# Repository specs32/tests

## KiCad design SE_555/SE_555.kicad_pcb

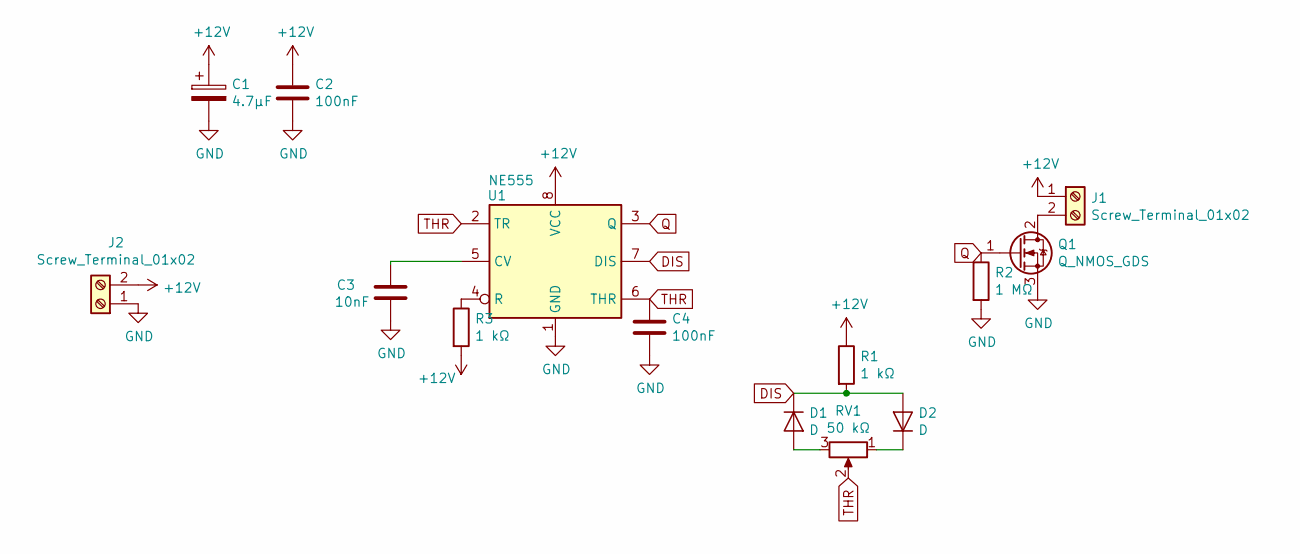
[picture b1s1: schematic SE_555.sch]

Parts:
C1: 4.7µF; CP_Radial_D6.3mm_P2.50mm
C2, C4: 100nF; C_Disc_D4.7mm_W2.5mm_P5.00mm
C3: 10nF; C_Disc_D4.7mm_W2.5mm_P5.00mm
D1, D2: D; D_A-405_P7.62mm_Horizontal
J1, J2: Screw_Terminal_01x02; TerminalBlock_bornier-2_P5.08mm
Q1: Q_NMOS_GDS; TO-220-3_Vertical
R1, R3: 1 kΩ; R_Axial_DIN0207_L6.3mm_D2.5mm_P7.62mm_Horizontal
R2: 1 MΩ; R_Axial_DIN0207_L6.3mm_D2.5mm_P7.62mm_Horizontal
RV1: 50 kΩ; Potentiometer_Bourns_3386C_Horizontal
U1: NE555; DIP-8_W7.62mm_LongPads

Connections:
+12V: C1.1, C2.1, J1.1, J2.2, R1.1, R3.2, U1.8 (VCC)
DIS: D1.1 (K), D2.2 (A), R1.2, U1.7 (DIS)
GND: C1.2, C2.2, C3.1, C4.2, J2.1, Q1.3 (S), R2.2, U1.1 (GND)
unnamed: C3.2, U1.5 (CV)
unnamed: D1.2 (A), RV1.3
unnamed: D2.1 (K), RV1.1
unnamed: J1.2, Q1.2 (D)
unnamed: R3.1, U1.4 (R)
Q: Q1.1 (G), R2.1, U1.3 (Q)
THR: C4.1, RV1.2, U1.2 (TR), U1.6 (THR)

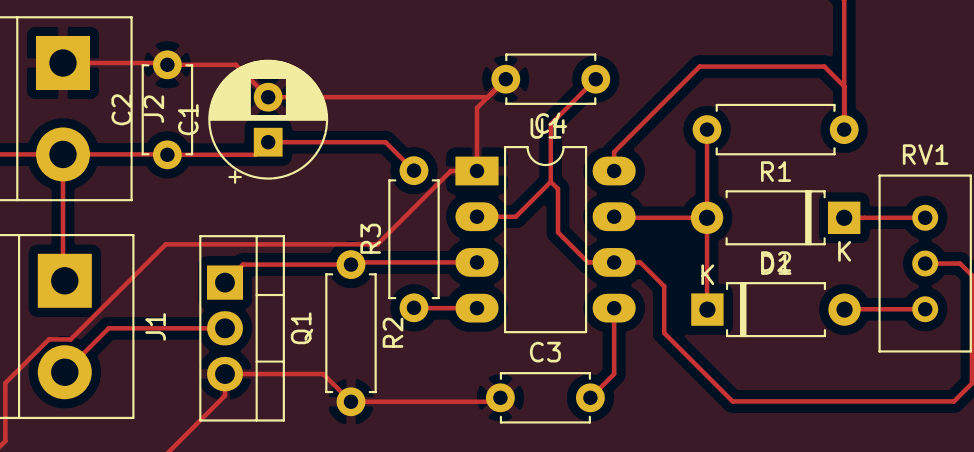
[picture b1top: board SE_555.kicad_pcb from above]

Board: 2 copper layers, 14 parts (0 on the bottom side), 10 nets.

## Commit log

2020-01-25 updated kiCAD
